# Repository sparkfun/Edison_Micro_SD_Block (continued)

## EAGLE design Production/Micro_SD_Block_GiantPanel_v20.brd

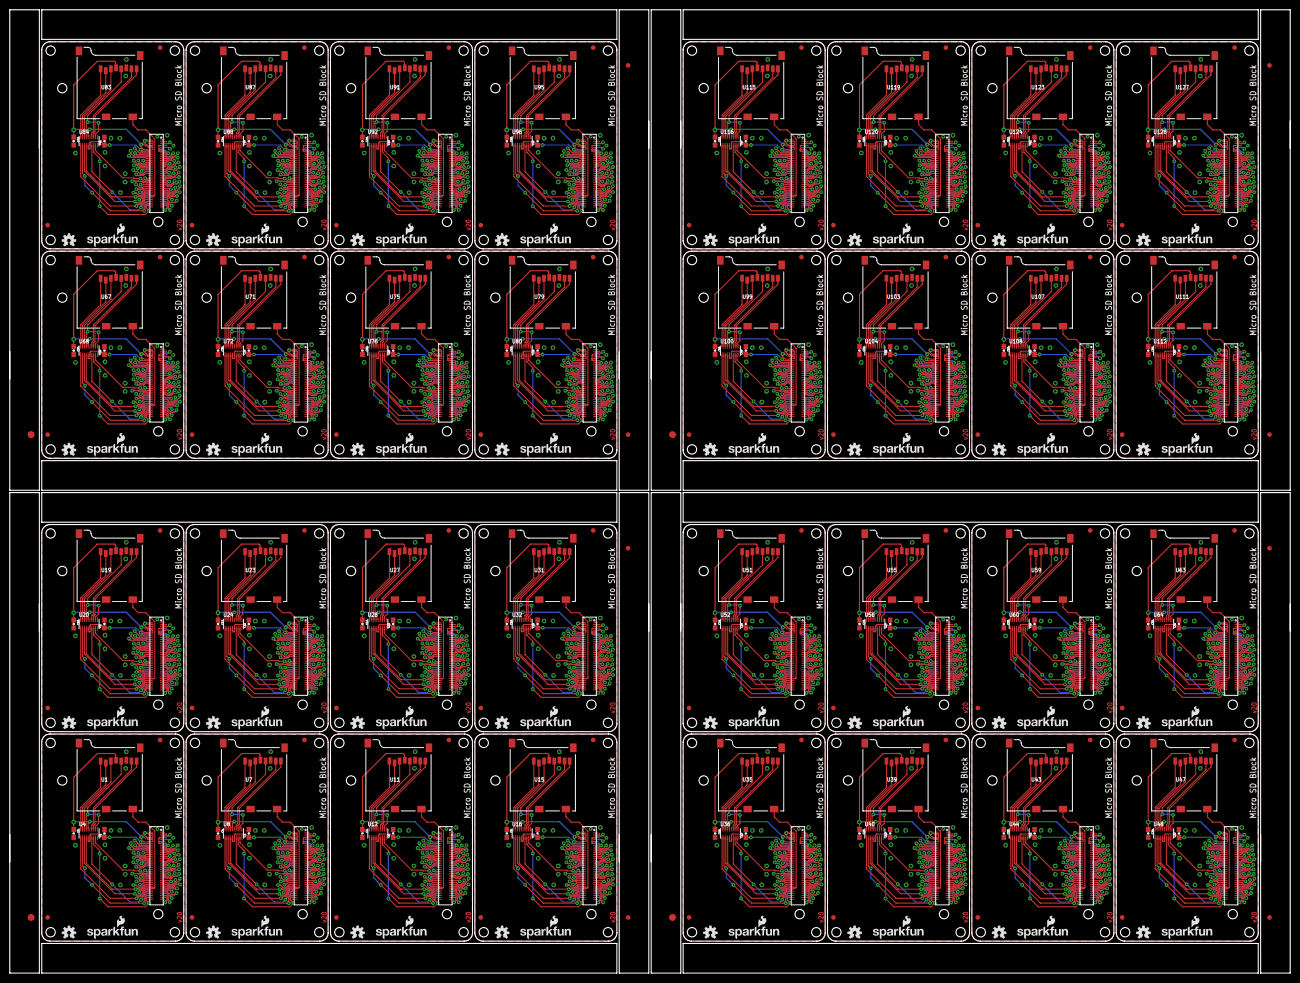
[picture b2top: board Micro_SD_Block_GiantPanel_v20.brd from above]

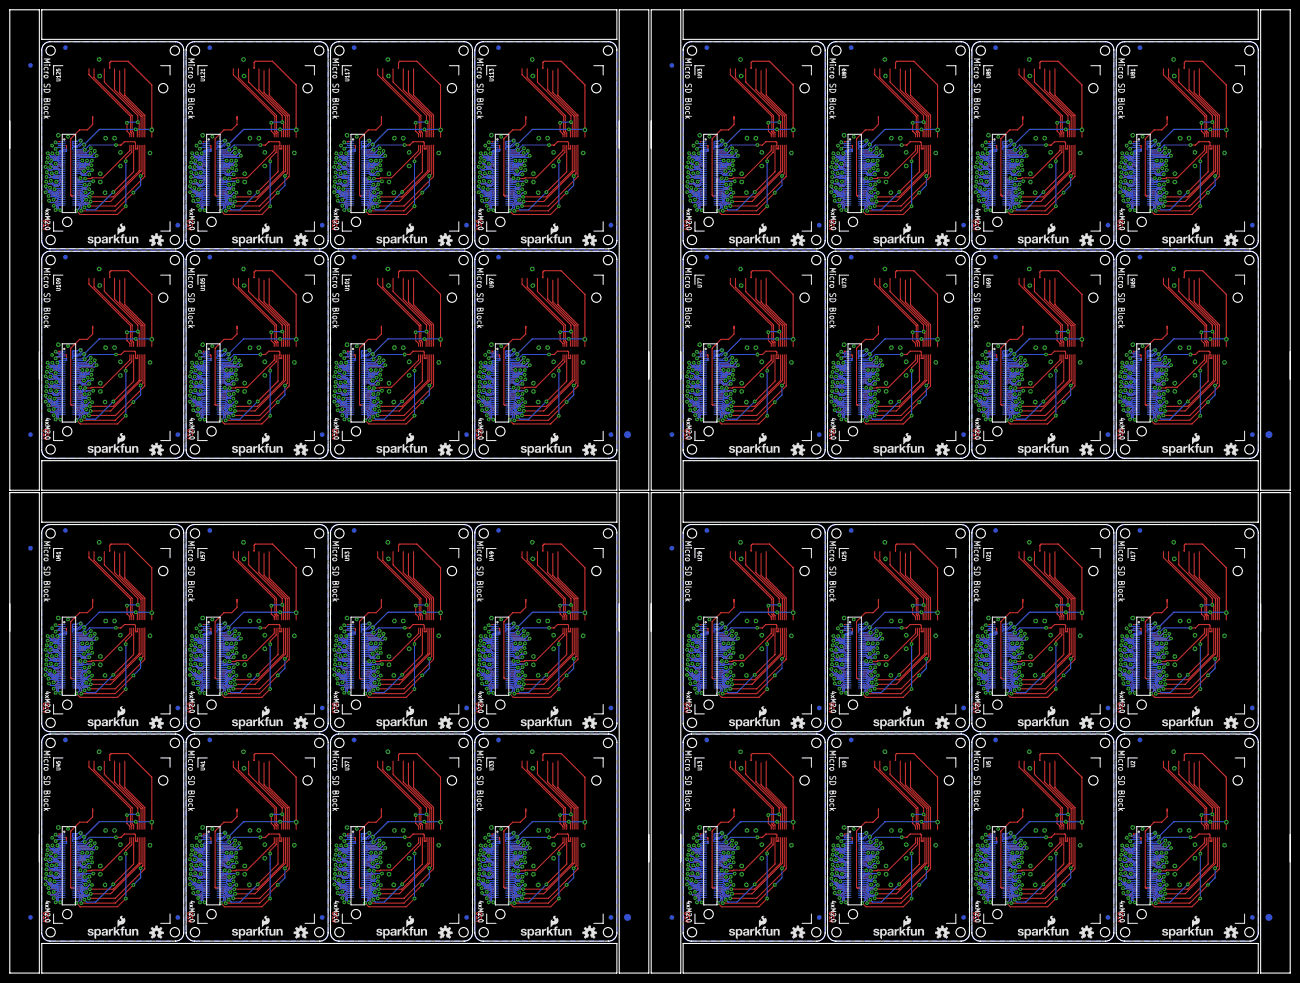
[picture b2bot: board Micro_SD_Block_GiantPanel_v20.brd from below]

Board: 2 copper layers, 274.8 x 206.8 mm, 472 parts (204 on the bottom side), 2048 nets.

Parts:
C1, C2, C3, C4, C5, C6, C7, C8, C9, C10, C11, C12, C13, C14, C15, C16, C17, C18, C19, C20, C21, C22, C23, C24, C25, C26, C27, C28, C29, C30, C31, C32, C33, C34, C35, C36, C37, C38, C39, C40, C41, C42, C43, C44, C45, C46, C47, C48, C49, C50, C51, C52, C53, C54, C55, C56, C57, C58, C59, C60, C61, C62, C63, C64: 0.1uF; 0603-CAP
E$1, E$2, E$9, E$10, E$15, E$16, E$21, E$22: FIDUCIAL-1.5X3
E$3, E$4, E$5, E$6, E$7, E$8, E$11, E$12, E$13, E$14, E$17, E$18, E$19, E$20, E$23, E$24: FIDUCIAL-1X2
FID1, FID2, FID3, FID4, FID5, FID6, FID7, FID8, FID9, FID10, FID11, FID12, FID13, FID14, FID15, FID16, FID17, FID18, FID19, FID20, FID21, FID22, FID23, FID24, FID25, FID26, FID27, FID28, FID29, FID30, FID31, FID32, FID33, FID34, FID35, FID36, FID37, FID38, FID39, FID40, FID41, FID42, FID43, FID44, FID45, FID46, FID47, FID48, FID49, FID50, FID51, FID52, FID53, FID54, FID55, FID56, FID57, FID58, FID59, FID60, FID61, FID62, FID63, FID64, FID65, FID66, FID67, FID68, FID69, FID70, FID71, FID72, FID73, FID74, FID75, FID76, FID77, FID78, FID79, FID80, FID81, FID82, FID83, FID84, FID85, FID86, FID87, FID88, FID89, FID90, FID91, FID92, FID93, FID94, FID95, FID96, FID97, FID98, FID99, FID100, FID101, FID102, FID103, FID104, FID105, FID106, FID107, FID108, FID109, FID110, FID111, FID112, FID113, FID114, FID115, FID116, FID117, FID118, FID119, FID120, FID121, FID122, FID123, FID124, FID125, FID126, FID127, FID128: FIDUCIAL1X2; FIDUCIAL-1X2
LOGO1, LOGO2, LOGO5, LOGO7, LOGO9, LOGO11, LOGO13, LOGO15, LOGO17, LOGO19, LOGO21, LOGO23, LOGO25, LOGO27, LOGO29, LOGO31, LOGO33, LOGO35, LOGO37, LOGO39, LOGO41, LOGO43, LOGO45, LOGO47, LOGO49, LOGO51, LOGO53, LOGO55, LOGO57, LOGO59, LOGO61, LOGO63, LOGO65, LOGO67, LOGO69, LOGO71, LOGO73, LOGO75, LOGO77, LOGO79, LOGO81, LOGO83, LOGO85, LOGO87, LOGO89, LOGO91, LOGO93, LOGO95, LOGO97, LOGO99, LOGO101, LOGO103, LOGO105, LOGO107, LOGO109, LOGO111, LOGO113, LOGO115, LOGO117, LOGO119, LOGO121, LOGO123, LOGO125, LOGO127: OSHW-LOGOS; OSHW-LOGO-S
LOGO3, LOGO4, LOGO6, LOGO8, LOGO10, LOGO12, LOGO14, LOGO16, LOGO18, LOGO20, LOGO22, LOGO24, LOGO26, LOGO28, LOGO30, LOGO32, LOGO34, LOGO36, LOGO38, LOGO40, LOGO42, LOGO44, LOGO46, LOGO48, LOGO50, LOGO52, LOGO54, LOGO56, LOGO58, LOGO60, LOGO62, LOGO64, LOGO66, LOGO68, LOGO70, LOGO72, LOGO74, LOGO76, LOGO78, LOGO80, LOGO82, LOGO84, LOGO86, LOGO88, LOGO90, LOGO92, LOGO94, LOGO96, LOGO98, LOGO100, LOGO102, LOGO104, LOGO106, LOGO108, LOGO110, LOGO112, LOGO114, LOGO116, LOGO118, LOGO120, LOGO122, LOGO124, LOGO126, LOGO128: SFE_LOGO_NAME_FLAME.1_INCH; SFE_LOGO_NAME_FLAME_.1
U1, U7, U11, U15, U19, U23, U27, U31, U35, U39, U43, U47, U51, U55, U59, U63, U67, U71, U75, U79, U83, U87, U91, U95, U99, U103, U107, U111, U115, U119, U123, U127: USD-SOCKETNEW; MICRO-SD-SOCKET-PP
U2, U5, U9, U13, U17, U21, U25, U29, U33, U37, U41, U45, U49, U53, U57, U61, U65, U69, U73, U77, U81, U85, U89, U93, U97, U101, U105, U109, U113, U117, U121, U125: EDISON_CONNECTOR_FULLMOUNTING_HOLES; EDISON_DAUGHTER
U3, U6, U10, U14, U18, U22, U26, U30, U34, U38, U42, U46, U50, U54, U58, U62, U66, U70, U74, U78, U82, U86, U90, U94, U98, U102, U106, U110, U114, U118, U122, U126: EDISON_CONNECTOR_FULLHEADER; DF40C-70DP-0.4(51)
U4, U8, U12, U16, U20, U24, U28, U32, U36, U40, U44, U48, U52, U56, U60, U64, U68, U72, U76, U80, U84, U88, U92, U96, U100, U104, U108, U112, U116, U120, U124, U128: TXB0108; UFDFN-20

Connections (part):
1.8V: C1.1, U2.12, U3.12, U4.P$5, U4.P$6
1.8V1: C3.1, U5.12, U6.12, U8.P$5, U8.P$6
1.8V2: C5.1, U9.12, U10.12, U12.P$5, U12.P$6
1.8V3: C7.1, U13.12, U14.12, U16.P$5, U16.P$6
1.8V4: C9.1, U17.12, U18.12, U20.P$5, U20.P$6
1.8V5: C11.1, U21.12, U22.12, U24.P$5, U24.P$6
1.8V6: C13.1, U25.12, U26.12, U28.P$5, U28.P$6
1.8V7: C15.1, U29.12, U30.12, U32.P$5, U32.P$6
1.8V8: C17.1, U33.12, U34.12, U36.P$5, U36.P$6
1.8V9: C19.1, U37.12, U38.12, U40.P$5, U40.P$6
1.8V10: C21.1, U41.12, U42.12, U44.P$5, U44.P$6
1.8V11: C23.1, U45.12, U46.12, U48.P$5, U48.P$6
1.8V12: C25.1, U49.12, U50.12, U52.P$5, U52.P$6
1.8V13: C27.1, U53.12, U54.12, U56.P$5, U56.P$6
1.8V14: C29.1, U57.12, U58.12, U60.P$5, U60.P$6
1.8V15: C31.1, U61.12, U62.12, U64.P$5, U64.P$6
1.8V16: C33.1, U65.12, U66.12, U68.P$5, U68.P$6
1.8V17: C35.1, U69.12, U70.12, U72.P$5, U72.P$6
1.8V18: C37.1, U73.12, U74.12, U76.P$5, U76.P$6
1.8V19: C39.1, U77.12, U78.12, U80.P$5, U80.P$6
1.8V20: C41.1, U81.12, U82.12, U84.P$5, U84.P$6
1.8V21: C43.1, U85.12, U86.12, U88.P$5, U88.P$6
1.8V22: C45.1, U89.12, U90.12, U92.P$5, U92.P$6
1.8V23: C47.1, U93.12, U94.12, U96.P$5, U96.P$6
1.8V24: C49.1, U97.12, U98.12, U100.P$5, U100.P$6
1.8V25: C51.1, U101.12, U102.12, U104.P$5, U104.P$6
1.8V26: C53.1, U105.12, U106.12, U108.P$5, U108.P$6
1.8V27: C55.1, U109.12, U110.12, U112.P$5, U112.P$6
1.8V28: C57.1, U113.12, U114.12, U116.P$5, U116.P$6
1.8V29: C59.1, U117.12, U118.12, U120.P$5, U120.P$6
1.8V30: C61.1, U121.12, U122.12, U124.P$5, U124.P$6
1.8V31: C63.1, U125.12, U126.12, U128.P$5, U128.P$6
3.3V: C2.1, U1.4, U2.8, U2.10, U3.8, U3.10, U4.P$16
3.3V1: C4.1, U5.8, U5.10, U6.8, U6.10, U7.4, U8.P$16
3.3V2: C6.1, U9.8, U9.10, U10.8, U10.10, U11.4, U12.P$16
3.3V3: C8.1, U13.8, U13.10, U14.8, U14.10, U15.4, U16.P$16
3.3V4: C10.1, U17.8, U17.10, U18.8, U18.10, U19.4, U20.P$16
3.3V5: C12.1, U21.8, U21.10, U22.8, U22.10, U23.4, U24.P$16
3.3V6: C14.1, U25.8, U25.10, U26.8, U26.10, U27.4, U28.P$16
3.3V7: C16.1, U29.8, U29.10, U30.8, U30.10, U31.4, U32.P$16
3.3V8: C18.1, U33.8, U33.10, U34.8, U34.10, U35.4, U36.P$16
3.3V9: C20.1, U37.8, U37.10, U38.8, U38.10, U39.4, U40.P$16
3.3V10: C22.1, U41.8, U41.10, U42.8, U42.10, U43.4, U44.P$16
3.3V11: C24.1, U45.8, U45.10, U46.8, U46.10, U47.4, U48.P$16
3.3V12: C26.1, U49.8, U49.10, U50.8, U50.10, U51.4, U52.P$16
3.3V13: C28.1, U53.8, U53.10, U54.8, U54.10, U55.4, U56.P$16
3.3V14: C30.1, U57.8, U57.10, U58.8, U58.10, U59.4, U60.P$16
3.3V15: C32.1, U61.8, U61.10, U62.8, U62.10, U63.4, U64.P$16
3.3V16: C34.1, U65.8, U65.10, U66.8, U66.10, U67.4, U68.P$16
3.3V17: C36.1, U69.8, U69.10, U70.8, U70.10, U71.4, U72.P$16
3.3V18: C38.1, U73.8, U73.10, U74.8, U74.10, U75.4, U76.P$16
3.3V19: C40.1, U77.8, U77.10, U78.8, U78.10, U79.4, U80.P$16
3.3V20: C42.1, U81.8, U81.10, U82.8, U82.10, U83.4, U84.P$16
3.3V21: C44.1, U85.8, U85.10, U86.8, U86.10, U87.4, U88.P$16
3.3V22: C46.1, U89.8, U89.10, U90.8, U90.10, U91.4, U92.P$16
3.3V23: C48.1, U93.8, U93.10, U94.8, U94.10, U95.4, U96.P$16
3.3V24: C50.1, U97.8, U97.10, U98.8, U98.10, U99.4, U100.P$16
3.3V25: C52.1, U101.8, U101.10, U102.8, U102.10, U103.4, U104.P$16
3.3V26: C54.1, U105.8, U105.10, U106.8, U106.10, U107.4, U108.P$16
3.3V27: C56.1, U109.8, U109.10, U110.8, U110.10, U111.4, U112.P$16
3.3V28: C58.1, U113.8, U113.10, U114.8, U114.10, U115.4, U116.P$16
3.3V29: C60.1, U117.8, U117.10, U118.8, U118.10, U119.4, U120.P$16
3.3V30: C62.1, U121.8, U121.10, U122.8, U122.10, U123.4, U124.P$16
3.3V31: C64.1, U125.8, U125.10, U126.8, U126.10, U127.4, U128.P$16
DCIN: U2.14, U3.14
DCIN1: U5.14, U6.14
DCIN2: U9.14, U10.14
DCIN3: U13.14, U14.14
DCIN4: U17.14, U18.14
DCIN5: U21.14, U22.14
DCIN6: U25.14, U26.14
DCIN7: U29.14, U30.14
DCIN8: U33.14, U34.14
DCIN9: U37.14, U38.14
DCIN10: U41.14, U42.14
DCIN11: U45.14, U46.14
DCIN12: U49.14, U50.14
DCIN13: U53.14, U54.14
DCIN14: U57.14, U58.14
DCIN15: U61.14, U62.14
DCIN16: U65.14, U66.14
DCIN17: U69.14, U70.14
DCIN18: U73.14, U74.14
DCIN19: U77.14, U78.14
DCIN20: U81.14, U82.14
DCIN21: U85.14, U86.14
DCIN22: U89.14, U90.14
DCIN23: U93.14, U94.14
DCIN24: U97.14, U98.14
DCIN25: U101.14, U102.14
DCIN26: U105.14, U106.14
DCIN27: U109.14, U110.14
DCIN28: U113.14, U114.14
DCIN29: U117.14, U118.14
DCIN30: U121.14, U122.14
DCIN31: U125.14, U126.14
FAULT: U2.19, U3.19
FAULT1: U5.19, U6.19
FAULT2: U9.19, U10.19
FAULT3: U13.19, U14.19
FAULT4: U17.19, U18.19
FAULT5: U21.19, U22.19
FAULT6: U25.19, U26.19
FAULT7: U29.19, U30.19
FAULT8: U33.19, U34.19
FAULT9: U37.19, U38.19
FAULT10: U41.19, U42.19
FAULT11: U45.19, U46.19
FAULT12: U49.19, U50.19
FAULT13: U53.19, U54.19
FAULT14: U57.19, U58.19
FAULT15: U61.19, U62.19
FAULT16: U65.19, U66.19
FAULT17: U69.19, U70.19
FAULT18: U73.19, U74.19
FAULT19: U77.19, U78.19
FAULT20: U81.19, U82.19
FAULT21: U85.19, U86.19
FAULT22: U89.19, U90.19
FAULT23: U93.19, U94.19
FAULT24: U97.19, U98.19
FAULT25: U101.19, U102.19
FAULT26: U105.19, U106.19
FAULT27: U109.19, U110.19
FAULT28: U113.19, U114.19
FAULT29: U117.19, U118.19
FAULT30: U121.19, U122.19
FAULT31: U125.19, U126.19
FW_RCVR: U2.69, U3.69
FW_RCVR1: U5.69, U6.69
FW_RCVR2: U9.69, U10.69
FW_RCVR3: U13.69, U14.69
FW_RCVR4: U17.69, U18.69
FW_RCVR5: U21.69, U22.69
FW_RCVR6: U25.69, U26.69
FW_RCVR7: U29.69, U30.69
FW_RCVR8: U33.69, U34.69
FW_RCVR9: U37.69, U38.69
FW_RCVR10: U41.69, U42.69
FW_RCVR11: U45.69, U46.69
FW_RCVR12: U49.69, U50.69
FW_RCVR13: U53.69, U54.69
FW_RCVR14: U57.69, U58.69
FW_RCVR15: U61.69, U62.69
FW_RCVR16: U65.69, U66.69
FW_RCVR17: U69.69, U70.69
FW_RCVR18: U73.69, U74.69
FW_RCVR19: U77.69, U78.69
FW_RCVR20: U81.69, U82.69
FW_RCVR21: U85.69, U86.69
FW_RCVR22: U89.69, U90.69
FW_RCVR23: U93.69, U94.69
FW_RCVR24: U97.69, U98.69
FW_RCVR25: U101.69, U102.69
FW_RCVR26: U105.69, U106.69
FW_RCVR27: U109.69, U110.69
FW_RCVR28: U113.69, U114.69
FW_RCVR29: U117.69, U118.69
FW_RCVR30: U121.69, U122.69
FW_RCVR31: U125.69, U126.69
GND: C1.2, C2.2, U1.6, U1.GND1, U1.GND3, U2.1, U2.5, U2.9, U2.11, U2.13, U2.15, U3.1, U3.5, U3.9, U3.11, U3.13, U3.15, U4.P$15
GND1: C3.2, C4.2, U5.1, U5.5, U5.9, U5.11, U5.13, U5.15, U6.1, U6.5, U6.9, U6.11, U6.13, U6.15, U7.6, U7.GND1, U7.GND3, U8.P$15
GND2: C5.2, C6.2, U9.1, U9.5, U9.9, U9.11, U9.13, U9.15, U10.1, U10.5, U10.9, U10.11, U10.13, U10.15, U11.6, U11.GND1, U11.GND3, U12.P$15
GND3: C7.2, C8.2, U13.1, U13.5, U13.9, U13.11, U13.13, U13.15, U14.1, U14.5, U14.9, U14.11, U14.13, U14.15, U15.6, U15.GND1, U15.GND3, U16.P$15
GND4: C9.2, C10.2, U17.1, U17.5, U17.9, U17.11, U17.13, U17.15, U18.1, U18.5, U18.9, U18.11, U18.13, U18.15, U19.6, U19.GND1, U19.GND3, U20.P$15
GND5: C11.2, C12.2, U21.1, U21.5, U21.9, U21.11, U21.13, U21.15, U22.1, U22.5, U22.9, U22.11, U22.13, U22.15, U23.6, U23.GND1, U23.GND3, U24.P$15
GND6: C13.2, C14.2, U25.1, U25.5, U25.9, U25.11, U25.13, U25.15, U26.1, U26.5, U26.9, U26.11, U26.13, U26.15, U27.6, U27.GND1, U27.GND3, U28.P$15
GND7: C15.2, C16.2, U29.1, U29.5, U29.9, U29.11, U29.13, U29.15, U30.1, U30.5, U30.9, U30.11, U30.13, U30.15, U31.6, U31.GND1, U31.GND3, U32.P$15
GND8: C17.2, C18.2, U33.1, U33.5, U33.9, U33.11, U33.13, U33.15, U34.1, U34.5, U34.9, U34.11, U34.13, U34.15, U35.6, U35.GND1, U35.GND3, U36.P$15
GND9: C19.2, C20.2, U37.1, U37.5, U37.9, U37.11, U37.13, U37.15, U38.1, U38.5, U38.9, U38.11, U38.13, U38.15, U39.6, U39.GND1, U39.GND3, U40.P$15
GND10: C21.2, C22.2, U41.1, U41.5, U41.9, U41.11, U41.13, U41.15, U42.1, U42.5, U42.9, U42.11, U42.13, U42.15, U43.6, U43.GND1, U43.GND3, U44.P$15
GND11: C23.2, C24.2, U45.1, U45.5, U45.9, U45.11, U45.13, U45.15, U46.1, U46.5, U46.9, U46.11, U46.13, U46.15, U47.6, U47.GND1, U47.GND3, U48.P$15
GND12: C25.2, C26.2, U49.1, U49.5, U49.9, U49.11, U49.13, U49.15, U50.1, U50.5, U50.9, U50.11, U50.13, U50.15, U51.6, U51.GND1, U51.GND3, U52.P$15
GND13: C27.2, C28.2, U53.1, U53.5, U53.9, U53.11, U53.13, U53.15, U54.1, U54.5, U54.9, U54.11, U54.13, U54.15, U55.6, U55.GND1, U55.GND3, U56.P$15
GND14: C29.2, C30.2, U57.1, U57.5, U57.9, U57.11, U57.13, U57.15, U58.1, U58.5, U58.9, U58.11, U58.13, U58.15, U59.6, U59.GND1, U59.GND3, U60.P$15
GND15: C31.2, C32.2, U61.1, U61.5, U61.9, U61.11, U61.13, U61.15, U62.1, U62.5, U62.9, U62.11, U62.13, U62.15, U63.6, U63.GND1, U63.GND3, U64.P$15
GND16: C33.2, C34.2, U65.1, U65.5, U65.9, U65.11, U65.13, U65.15, U66.1, U66.5, U66.9, U66.11, U66.13, U66.15, U67.6, U67.GND1, U67.GND3, U68.P$15
GND17: C35.2, C36.2, U69.1, U69.5, U69.9, U69.11, U69.13, U69.15, U70.1, U70.5, U70.9, U70.11, U70.13, U70.15, U71.6, U71.GND1, U71.GND3, U72.P$15
GND18: C37.2, C38.2, U73.1, U73.5, U73.9, U73.11, U73.13, U73.15, U74.1, U74.5, U74.9, U74.11, U74.13, U74.15, U75.6, U75.GND1, U75.GND3, U76.P$15
GND19: C39.2, C40.2, U77.1, U77.5, U77.9, U77.11, U77.13, U77.15, U78.1, U78.5, U78.9, U78.11, U78.13, U78.15, U79.6, U79.GND1, U79.GND3, U80.P$15
GND20: C41.2, C42.2, U81.1, U81.5, U81.9, U81.11, U81.13, U81.15, U82.1, U82.5, U82.9, U82.11, U82.13, U82.15, U83.6, U83.GND1, U83.GND3, U84.P$15
GND21: C43.2, C44.2, U85.1, U85.5, U85.9, U85.11, U85.13, U85.15, U86.1, U86.5, U86.9, U86.11, U86.13, U86.15, U87.6, U87.GND1, U87.GND3, U88.P$15
GND22: C45.2, C46.2, U89.1, U89.5, U89.9, U89.11, U89.13, U89.15, U90.1, U90.5, U90.9, U90.11, U90.13, U90.15, U91.6, U91.GND1, U91.GND3, U92.P$15
GND23: C47.2, C48.2, U93.1, U93.5, U93.9, U93.11, U93.13, U93.15, U94.1, U94.5, U94.9, U94.11, U94.13, U94.15, U95.6, U95.GND1, U95.GND3, U96.P$15
GND24: C49.2, C50.2, U97.1, U97.5, U97.9, U97.11, U97.13, U97.15, U98.1, U98.5, U98.9, U98.11, U98.13, U98.15, U99.6, U99.GND1, U99.GND3, U100.P$15
GND25: C51.2, C52.2, U101.1, U101.5, U101.9, U101.11, U101.13, U101.15, U102.1, U102.5, U102.9, U102.11, U102.13, U102.15, U103.6, U103.GND1, U103.GND3, U104.P$15
GND26: C53.2, C54.2, U105.1, U105.5, U105.9, U105.11, U105.13, U105.15, U106.1, U106.5, U106.9, U106.11, U106.13, U106.15, U107.6, U107.GND1, U107.GND3, U108.P$15
GND27: C55.2, C56.2, U109.1, U109.5, U109.9, U109.11, U109.13, U109.15, U110.1, U110.5, U110.9, U110.11, U110.13, U110.15, U111.6, U111.GND1, U111.GND3, U112.P$15
GND28: C57.2, C58.2, U113.1, U113.5, U113.9, U113.11, U113.13, U113.15, U114.1, U114.5, U114.9, U114.11, U114.13, U114.15, U115.6, U115.GND1, U115.GND3, U116.P$15
GND29: C59.2, C60.2, U117.1, U117.5, U117.9, U117.11, U117.13, U117.15, U118.1, U118.5, U118.9, U118.11, U118.13, U118.15, U119.6, U119.GND1, U119.GND3, U120.P$15
GND30: C61.2, C62.2, U121.1, U121.5, U121.9, U121.11, U121.13, U121.15, U122.1, U122.5, U122.9, U122.11, U122.13, U122.15, U123.6, U123.GND1, U123.GND3, U124.P$15
GND31: C63.2, C64.2, U125.1, U125.5, U125.9, U125.11, U125.13, U125.15, U126.1, U126.5, U126.9, U126.11, U126.13, U126.15, U127.6, U127.GND1, U127.GND3, U128.P$15
GP1: U5.48, U6.48
GP2: U5.42, U6.42
GP3: U5.34, U6.34
GP4: U5.32, U6.32
GP5: U5.30, U6.30
GP6: U5.28, U6.28
GP7: U5.26, U6.26
GP8: U5.25, U6.25
GP9: U5.24, U6.24
GP10: U9.48, U10.48
GP11: U9.42, U10.42
GP12: U9.34, U10.34
GP12_PWM0: U2.35, U3.35
GP12_PWM1: U5.35, U6.35
GP12_PWM2: U9.35, U10.35
GP12_PWM3: U13.35, U14.35
GP12_PWM4: U17.35, U18.35
GP12_PWM5: U21.35, U22.35
GP12_PWM6: U25.35, U26.35
GP12_PWM7: U29.35, U30.35
GP12_PWM8: U33.35, U34.35
GP12_PWM9: U37.35, U38.35
GP12_PWM10: U41.35, U42.35
GP12_PWM11: U45.35, U46.35
GP12_PWM12: U49.35, U50.35
GP12_PWM13: U53.35, U54.35
GP12_PWM14: U57.35, U58.35
GP12_PWM15: U61.35, U62.35
GP12_PWM16: U65.35, U66.35
GP12_PWM17: U69.35, U70.35
GP12_PWM18: U73.35, U74.35
GP12_PWM19: U77.35, U78.35
GP12_PWM20: U81.35, U82.35
GP12_PWM21: U85.35, U86.35
GP12_PWM22: U89.35, U90.35
GP12_PWM23: U93.35, U94.35
GP12_PWM24: U97.35, U98.35
GP12_PWM25: U101.35, U102.35
GP12_PWM26: U105.35, U106.35
GP12_PWM27: U109.35, U110.35
GP12_PWM28: U113.35, U114.35
GP12_PWM29: U117.35, U118.35
GP12_PWM30: U121.35, U122.35
GP12_PWM31: U125.35, U126.35
GP13: U9.32, U10.32
GP13_PWM1: U2.33, U3.33
GP13_PWM2: U5.33, U6.33
GP13_PWM3: U9.33, U10.33
GP13_PWM4: U13.33, U14.33
GP13_PWM5: U17.33, U18.33
GP13_PWM6: U21.33, U22.33
GP13_PWM7: U25.33, U26.33
GP13_PWM8: U29.33, U30.33
GP13_PWM9: U33.33, U34.33
GP13_PWM10: U37.33, U38.33
GP13_PWM11: U41.33, U42.33
GP13_PWM12: U45.33, U46.33
GP13_PWM13: U49.33, U50.33
GP13_PWM14: U53.33, U54.33
GP13_PWM15: U57.33, U58.33
GP13_PWM16: U61.33, U62.33
GP13_PWM17: U65.33, U66.33
GP13_PWM18: U69.33, U70.33
GP13_PWM19: U73.33, U74.33
GP13_PWM20: U77.33, U78.33
GP13_PWM21: U81.33, U82.33
GP13_PWM22: U85.33, U86.33
GP13_PWM23: U89.33, U90.33
GP13_PWM24: U93.33, U94.33
GP13_PWM25: U97.33, U98.33
GP13_PWM26: U101.33, U102.33
GP13_PWM27: U105.33, U106.33
GP13_PWM28: U109.33, U110.33
GP13_PWM29: U113.33, U114.33
GP13_PWM30: U117.33, U118.33
GP13_PWM31: U121.33, U122.33
GP13_PWM32: U125.33, U126.33
GP14: U2.48, U3.48
GP15: U2.42, U3.42
GP16: U9.30, U10.30
GP17: U9.28, U10.28
GP18: U9.26, U10.26
GP19: U9.25, U10.25
GP19_I2C_1_SCL: U2.41, U3.41
GP19_I2C_1_SCL1: U5.41, U6.41
GP19_I2C_1_SCL2: U9.41, U10.41
GP19_I2C_1_SCL3: U13.41, U14.41
GP19_I2C_1_SCL4: U17.41, U18.41
GP19_I2C_1_SCL5: U21.41, U22.41
GP19_I2C_1_SCL6: U25.41, U26.41
GP19_I2C_1_SCL7: U29.41, U30.41
GP19_I2C_1_SCL8: U33.41, U34.41
GP19_I2C_1_SCL9: U37.41, U38.41
GP19_I2C_1_SCL10: U41.41, U42.41
GP19_I2C_1_SCL11: U45.41, U46.41
GP19_I2C_1_SCL12: U49.41, U50.41
GP19_I2C_1_SCL13: U53.41, U54.41
GP19_I2C_1_SCL14: U57.41, U58.41
GP19_I2C_1_SCL15: U61.41, U62.41
GP19_I2C_1_SCL16: U65.41, U66.41
GP19_I2C_1_SCL17: U69.41, U70.41
GP19_I2C_1_SCL18: U73.41, U74.41
GP19_I2C_1_SCL19: U77.41, U78.41
GP19_I2C_1_SCL20: U81.41, U82.41
GP19_I2C_1_SCL21: U85.41, U86.41
GP19_I2C_1_SCL22: U89.41, U90.41
GP19_I2C_1_SCL23: U93.41, U94.41
GP19_I2C_1_SCL24: U97.41, U98.41
GP19_I2C_1_SCL25: U101.41, U102.41
GP19_I2C_1_SCL26: U105.41, U106.41
GP19_I2C_1_SCL27: U109.41, U110.41
GP19_I2C_1_SCL28: U113.41, U114.41
GP19_I2C_1_SCL29: U117.41, U118.41
GP19_I2C_1_SCL30: U121.41, U122.41
GP19_I2C_1_SCL31: U125.41, U126.41
GP20: U9.24, U10.24
GP20_I2C_1_SDA: U2.43, U3.43
GP20_I2C_1_SDA1: U5.43, U6.43
GP20_I2C_1_SDA2: U9.43, U10.43
GP20_I2C_1_SDA3: U13.43, U14.43
GP20_I2C_1_SDA4: U17.43, U18.43
GP20_I2C_1_SDA5: U21.43, U22.43
GP20_I2C_1_SDA6: U25.43, U26.43
GP20_I2C_1_SDA7: U29.43, U30.43
GP20_I2C_1_SDA8: U33.43, U34.43
GP20_I2C_1_SDA9: U37.43, U38.43
GP20_I2C_1_SDA10: U41.43, U42.43
GP20_I2C_1_SDA11: U45.43, U46.43
GP20_I2C_1_SDA12: U49.43, U50.43
GP20_I2C_1_SDA13: U53.43, U54.43
GP20_I2C_1_SDA14: U57.43, U58.43
GP20_I2C_1_SDA15: U61.43, U62.43
GP20_I2C_1_SDA16: U65.43, U66.43
GP20_I2C_1_SDA17: U69.43, U70.43
GP20_I2C_1_SDA18: U73.43, U74.43
GP20_I2C_1_SDA19: U77.43, U78.43
GP20_I2C_1_SDA20: U81.43, U82.43
GP20_I2C_1_SDA21: U85.43, U86.43
GP20_I2C_1_SDA22: U89.43, U90.43
GP20_I2C_1_SDA23: U93.43, U94.43
GP20_I2C_1_SDA24: U97.43, U98.43
GP20_I2C_1_SDA25: U101.43, U102.43
GP20_I2C_1_SDA26: U105.43, U106.43
GP20_I2C_1_SDA27: U109.43, U110.43
GP20_I2C_1_SDA28: U113.43, U114.43
GP20_I2C_1_SDA29: U117.43, U118.43
GP20_I2C_1_SDA30: U121.43, U122.43
GP20_I2C_1_SDA31: U125.43, U126.43
GP21: U13.48, U14.48
GP22: U13.42, U14.42
GP23: U13.34, U14.34
GP24: U13.32, U14.32
GP25: U13.30, U14.30
GP26: U13.28, U14.28
GP27: U13.26, U14.26
GP27_I2C_6_SCL: U2.45, U3.45
GP27_I2C_6_SCL1: U5.45, U6.45
GP27_I2C_6_SCL2: U9.45, U10.45
GP27_I2C_6_SCL3: U13.45, U14.45
GP27_I2C_6_SCL4: U17.45, U18.45
GP27_I2C_6_SCL5: U21.45, U22.45
GP27_I2C_6_SCL6: U25.45, U26.45
GP27_I2C_6_SCL7: U29.45, U30.45
GP27_I2C_6_SCL8: U33.45, U34.45
GP27_I2C_6_SCL9: U37.45, U38.45
GP27_I2C_6_SCL10: U41.45, U42.45
GP27_I2C_6_SCL11: U45.45, U46.45
GP27_I2C_6_SCL12: U49.45, U50.45
GP27_I2C_6_SCL13: U53.45, U54.45
GP27_I2C_6_SCL14: U57.45, U58.45
GP27_I2C_6_SCL15: U61.45, U62.45
GP27_I2C_6_SCL16: U65.45, U66.45
GP27_I2C_6_SCL17: U69.45, U70.45
GP27_I2C_6_SCL18: U73.45, U74.45
GP27_I2C_6_SCL19: U77.45, U78.45
GP27_I2C_6_SCL20: U81.45, U82.45
GP27_I2C_6_SCL21: U85.45, U86.45
GP27_I2C_6_SCL22: U89.45, U90.45
GP27_I2C_6_SCL23: U93.45, U94.45
GP27_I2C_6_SCL24: U97.45, U98.45
GP27_I2C_6_SCL25: U101.45, U102.45
GP27_I2C_6_SCL26: U105.45, U106.45
GP27_I2C_6_SCL27: U109.45, U110.45
GP27_I2C_6_SCL28: U113.45, U114.45
GP27_I2C_6_SCL29: U117.45, U118.45
GP27_I2C_6_SCL30: U121.45, U122.45
GP27_I2C_6_SCL31: U125.45, U126.45
GP28: U13.25, U14.25
GP28_I2C_6_SDA: U2.47, U3.47
GP28_I2C_6_SDA1: U5.47, U6.47
GP28_I2C_6_SDA2: U9.47, U10.47
GP28_I2C_6_SDA3: U13.47, U14.47
GP28_I2C_6_SDA4: U17.47, U18.47
GP28_I2C_6_SDA5: U21.47, U22.47
GP28_I2C_6_SDA6: U25.47, U26.47
GP28_I2C_6_SDA7: U29.47, U30.47
GP28_I2C_6_SDA8: U33.47, U34.47
GP28_I2C_6_SDA9: U37.47, U38.47
GP28_I2C_6_SDA10: U41.47, U42.47
GP28_I2C_6_SDA11: U45.47, U46.47
GP28_I2C_6_SDA12: U49.47, U50.47
GP28_I2C_6_SDA13: U53.47, U54.47
GP28_I2C_6_SDA14: U57.47, U58.47
GP28_I2C_6_SDA15: U61.47, U62.47
GP28_I2C_6_SDA16: U65.47, U66.47
GP28_I2C_6_SDA17: U69.47, U70.47
GP28_I2C_6_SDA18: U73.47, U74.47
GP28_I2C_6_SDA19: U77.47, U78.47
GP28_I2C_6_SDA20: U81.47, U82.47
GP28_I2C_6_SDA21: U85.47, U86.47
GP28_I2C_6_SDA22: U89.47, U90.47
GP28_I2C_6_SDA23: U93.47, U94.47
GP28_I2C_6_SDA24: U97.47, U98.47
GP28_I2C_6_SDA25: U101.47, U102.47
GP28_I2C_6_SDA26: U105.47, U106.47
GP28_I2C_6_SDA27: U109.47, U110.47
GP28_I2C_6_SDA28: U113.47, U114.47
GP28_I2C_6_SDA29: U117.47, U118.47
GP28_I2C_6_SDA30: U121.47, U122.47
GP28_I2C_6_SDA31: U125.47, U126.47
GP29: U13.24, U14.24
GP30: U17.48, U18.48
GP31: U17.42, U18.42
GP32: U17.34, U18.34
GP33: U17.32, U18.32
GP34: U17.30, U18.30
GP35: U17.28, U18.28
GP36: U17.26, U18.26
GP37: U17.25, U18.25
GP38: U17.24, U18.24
GP39: U21.48, U22.48
GP40: U21.42, U22.42
GP40_I2S_2_CLK: U2.52, U3.52
GP40_I2S_2_CLK1: U5.52, U6.52
GP40_I2S_2_CLK2: U9.52, U10.52
GP40_I2S_2_CLK3: U13.52, U14.52
GP40_I2S_2_CLK4: U17.52, U18.52
GP40_I2S_2_CLK5: U21.52, U22.52
GP40_I2S_2_CLK6: U25.52, U26.52
GP40_I2S_2_CLK7: U29.52, U30.52
GP40_I2S_2_CLK8: U33.52, U34.52
GP40_I2S_2_CLK9: U37.52, U38.52
GP40_I2S_2_CLK10: U41.52, U42.52
GP40_I2S_2_CLK11: U45.52, U46.52
GP40_I2S_2_CLK12: U49.52, U50.52
GP40_I2S_2_CLK13: U53.52, U54.52
GP40_I2S_2_CLK14: U57.52, U58.52
GP40_I2S_2_CLK15: U61.52, U62.52
GP40_I2S_2_CLK16: U65.52, U66.52
GP40_I2S_2_CLK17: U69.52, U70.52
GP40_I2S_2_CLK18: U73.52, U74.52
GP40_I2S_2_CLK19: U77.52, U78.52
GP40_I2S_2_CLK20: U81.52, U82.52
GP40_I2S_2_CLK21: U85.52, U86.52
GP40_I2S_2_CLK22: U89.52, U90.52
GP40_I2S_2_CLK23: U93.52, U94.52
GP40_I2S_2_CLK24: U97.52, U98.52
GP40_I2S_2_CLK25: U101.52, U102.52
GP40_I2S_2_CLK26: U105.52, U106.52
GP40_I2S_2_CLK27: U109.52, U110.52
GP40_I2S_2_CLK28: U113.52, U114.52
GP40_I2S_2_CLK29: U117.52, U118.52
GP40_I2S_2_CLK30: U121.52, U122.52
GP40_I2S_2_CLK31: U125.52, U126.52
GP41: U21.34, U22.34
GP41_I2S_2_FS: U2.54, U3.54
GP41_I2S_2_FS1: U5.54, U6.54
GP41_I2S_2_FS2: U9.54, U10.54
GP41_I2S_2_FS3: U13.54, U14.54
GP41_I2S_2_FS4: U17.54, U18.54
GP41_I2S_2_FS5: U21.54, U22.54
GP41_I2S_2_FS6: U25.54, U26.54
GP41_I2S_2_FS7: U29.54, U30.54
GP41_I2S_2_FS8: U33.54, U34.54
GP41_I2S_2_FS9: U37.54, U38.54
GP41_I2S_2_FS10: U41.54, U42.54
GP41_I2S_2_FS11: U45.54, U46.54
GP41_I2S_2_FS12: U49.54, U50.54
GP41_I2S_2_FS13: U53.54, U54.54
GP41_I2S_2_FS14: U57.54, U58.54
GP41_I2S_2_FS15: U61.54, U62.54
GP41_I2S_2_FS16: U65.54, U66.54
GP41_I2S_2_FS17: U69.54, U70.54
GP41_I2S_2_FS18: U73.54, U74.54
GP41_I2S_2_FS19: U77.54, U78.54
GP41_I2S_2_FS20: U81.54, U82.54
GP41_I2S_2_FS21: U85.54, U86.54
GP41_I2S_2_FS22: U89.54, U90.54
GP41_I2S_2_FS23: U93.54, U94.54
GP41_I2S_2_FS24: U97.54, U98.54
GP41_I2S_2_FS25: U101.54, U102.54
GP41_I2S_2_FS26: U105.54, U106.54
GP41_I2S_2_FS27: U109.54, U110.54
GP41_I2S_2_FS28: U113.54, U114.54
GP41_I2S_2_FS29: U117.54, U118.54
GP41_I2S_2_FS30: U121.54, U122.54
GP41_I2S_2_FS31: U125.54, U126.54
GP42: U21.32, U22.32
GP42_I2S_2_RXD: U2.50, U3.50
GP42_I2S_2_RXD1: U5.50, U6.50
GP42_I2S_2_RXD2: U9.50, U10.50
GP42_I2S_2_RXD3: U13.50, U14.50
GP42_I2S_2_RXD4: U17.50, U18.50
GP42_I2S_2_RXD5: U21.50, U22.50
GP42_I2S_2_RXD6: U25.50, U26.50
GP42_I2S_2_RXD7: U29.50, U30.50
GP42_I2S_2_RXD8: U33.50, U34.50
GP42_I2S_2_RXD9: U37.50, U38.50
GP42_I2S_2_RXD10: U41.50, U42.50
GP42_I2S_2_RXD11: U45.50, U46.50
GP42_I2S_2_RXD12: U49.50, U50.50
GP42_I2S_2_RXD13: U53.50, U54.50
GP42_I2S_2_RXD14: U57.50, U58.50
GP42_I2S_2_RXD15: U61.50, U62.50
GP42_I2S_2_RXD16: U65.50, U66.50
GP42_I2S_2_RXD17: U69.50, U70.50
GP42_I2S_2_RXD18: U73.50, U74.50
GP42_I2S_2_RXD19: U77.50, U78.50
GP42_I2S_2_RXD20: U81.50, U82.50
GP42_I2S_2_RXD21: U85.50, U86.50
GP42_I2S_2_RXD22: U89.50, U90.50
GP42_I2S_2_RXD23: U93.50, U94.50
GP42_I2S_2_RXD24: U97.50, U98.50
GP42_I2S_2_RXD25: U101.50, U102.50
GP42_I2S_2_RXD26: U105.50, U106.50
GP42_I2S_2_RXD27: U109.50, U110.50
GP42_I2S_2_RXD28: U113.50, U114.50
GP42_I2S_2_RXD29: U117.50, U118.50
GP42_I2S_2_RXD30: U121.50, U122.50
GP42_I2S_2_RXD31: U125.50, U126.50
GP43: U21.30, U22.30
GP43_I2S_2_TXD: U2.56, U3.56
GP43_I2S_2_TXD1: U5.56, U6.56
GP43_I2S_2_TXD2: U9.56, U10.56
GP43_I2S_2_TXD3: U13.56, U14.56
GP43_I2S_2_TXD4: U17.56, U18.56
GP43_I2S_2_TXD5: U21.56, U22.56
GP43_I2S_2_TXD6: U25.56, U26.56
GP43_I2S_2_TXD7: U29.56, U30.56
GP43_I2S_2_TXD8: U33.56, U34.56
GP43_I2S_2_TXD9: U37.56, U38.56
GP43_I2S_2_TXD10: U41.56, U42.56
GP43_I2S_2_TXD11: U45.56, U46.56
GP43_I2S_2_TXD12: U49.56, U50.56
GP43_I2S_2_TXD13: U53.56, U54.56
GP43_I2S_2_TXD14: U57.56, U58.56
GP43_I2S_2_TXD15: U61.56, U62.56
GP43_I2S_2_TXD16: U65.56, U66.56
GP43_I2S_2_TXD17: U69.56, U70.56
GP43_I2S_2_TXD18: U73.56, U74.56
GP43_I2S_2_TXD19: U77.56, U78.56
GP43_I2S_2_TXD20: U81.56, U82.56
GP43_I2S_2_TXD21: U85.56, U86.56
GP43_I2S_2_TXD22: U89.56, U90.56
GP43_I2S_2_TXD23: U93.56, U94.56
GP43_I2S_2_TXD24: U97.56, U98.56
GP43_I2S_2_TXD25: U101.56, U102.56
GP43_I2S_2_TXD26: U105.56, U106.56
GP43_I2S_2_TXD27: U109.56, U110.56
GP43_I2S_2_TXD28: U113.56, U114.56
GP43_I2S_2_TXD29: U117.56, U118.56
GP43_I2S_2_TXD30: U121.56, U122.56
GP43_I2S_2_TXD31: U125.56, U126.56
GP44: U2.24, U3.24
GP45: U2.26, U3.26
GP46: U2.28, U3.28
GP47: U2.30, U3.30
GP48: U2.32, U3.32
GP49: U2.34, U3.34
GP50: U21.28, U22.28
GP51: U21.26, U22.26
GP52: U21.25, U22.25
GP53: U21.24, U22.24
GP54: U25.48, U26.48
GP55: U25.42, U26.42
GP56: U25.34, U26.34
GP57: U25.32, U26.32
GP58: U25.30, U26.30
GP59: U25.28, U26.28
GP60: U25.26, U26.26
GP61: U25.25, U26.25
GP62: U25.24, U26.24
GP63: U29.48, U30.48
GP64: U29.42, U30.42
GP65: U29.34, U30.34
GP66: U29.32, U30.32
GP67: U29.30, U30.30
GP68: U29.28, U30.28
GP69: U29.26, U30.26
GP70: U29.25, U30.25
GP71: U29.24, U30.24
GP72: U33.48, U34.48
GP73: U33.42, U34.42
GP74: U33.34, U34.34
GP75: U33.32, U34.32
GP76: U33.30, U34.30
GP77: U33.28, U34.28
GP77_SD_0_CD#: U1.CD1, U2.60, U3.60
GP77_SD_0_CD#1: U5.60, U6.60, U7.CD1
GP77_SD_0_CD#2: U9.60, U10.60, U11.CD1
GP77_SD_0_CD#3: U13.60, U14.60, U15.CD1
GP77_SD_0_CD#4: U17.60, U18.60, U19.CD1
GP77_SD_0_CD#5: U21.60, U22.60, U23.CD1
GP77_SD_0_CD#6: U25.60, U26.60, U27.CD1
GP77_SD_0_CD#7: U29.60, U30.60, U31.CD1
GP77_SD_0_CD#8: U33.60, U34.60, U35.CD1
GP77_SD_0_CD#9: U37.60, U38.60, U39.CD1
GP77_SD_0_CD#10: U41.60, U42.60, U43.CD1
GP77_SD_0_CD#11: U45.60, U46.60, U47.CD1
GP77_SD_0_CD#12: U49.60, U50.60, U51.CD1
GP77_SD_0_CD#13: U53.60, U54.60, U55.CD1
GP77_SD_0_CD#14: U57.60, U58.60, U59.CD1
GP77_SD_0_CD#15: U61.60, U62.60, U63.CD1
GP77_SD_0_CD#16: U65.60, U66.60, U67.CD1
GP77_SD_0_CD#17: U69.60, U70.60, U71.CD1
GP77_SD_0_CD#18: U73.60, U74.60, U75.CD1
GP77_SD_0_CD#19: U77.60, U78.60, U79.CD1
GP77_SD_0_CD#20: U81.60, U82.60, U83.CD1
GP77_SD_0_CD#21: U85.60, U86.60, U87.CD1
GP77_SD_0_CD#22: U89.60, U90.60, U91.CD1
GP77_SD_0_CD#23: U93.60, U94.60, U95.CD1
GP77_SD_0_CD#24: U97.60, U98.60, U99.CD1
GP77_SD_0_CD#25: U101.60, U102.60, U103.CD1
GP77_SD_0_CD#26: U105.60, U106.60, U107.CD1
GP77_SD_0_CD#27: U109.60, U110.60, U111.CD1
GP77_SD_0_CD#28: U113.60, U114.60, U115.CD1
GP77_SD_0_CD#29: U117.60, U118.60, U119.CD1
GP77_SD_0_CD#30: U121.60, U122.60, U123.CD1
GP77_SD_0_CD#31: U125.60, U126.60, U127.CD1
GP78: U33.26, U34.26
GP78_SD_0_CLK: U2.58, U3.58, U4.P$4
GP78_SD_0_CLK1: U5.58, U6.58, U8.P$4
GP78_SD_0_CLK2: U9.58, U10.58, U12.P$4
GP78_SD_0_CLK3: U13.58, U14.58, U16.P$4
GP78_SD_0_CLK4: U17.58, U18.58, U20.P$4
GP78_SD_0_CLK5: U21.58, U22.58, U24.P$4
GP78_SD_0_CLK6: U25.58, U26.58, U28.P$4
GP78_SD_0_CLK7: U29.58, U30.58, U32.P$4
GP78_SD_0_CLK8: U33.58, U34.58, U36.P$4
GP78_SD_0_CLK9: U37.58, U38.58, U40.P$4
GP78_SD_0_CLK10: U41.58, U42.58, U44.P$4
GP78_SD_0_CLK11: U45.58, U46.58, U48.P$4
GP78_SD_0_CLK12: U49.58, U50.58, U52.P$4
GP78_SD_0_CLK13: U53.58, U54.58, U56.P$4
GP78_SD_0_CLK14: U57.58, U58.58, U60.P$4
GP78_SD_0_CLK15: U61.58, U62.58, U64.P$4
GP78_SD_0_CLK16: U65.58, U66.58, U68.P$4
GP78_SD_0_CLK17: U69.58, U70.58, U72.P$4
GP78_SD_0_CLK18: U73.58, U74.58, U76.P$4
GP78_SD_0_CLK19: U77.58, U78.58, U80.P$4
GP78_SD_0_CLK20: U81.58, U82.58, U84.P$4
GP78_SD_0_CLK21: U85.58, U86.58, U88.P$4
GP78_SD_0_CLK22: U89.58, U90.58, U92.P$4
GP78_SD_0_CLK23: U93.58, U94.58, U96.P$4
GP78_SD_0_CLK24: U97.58, U98.58, U100.P$4
GP78_SD_0_CLK25: U101.58, U102.58, U104.P$4
GP78_SD_0_CLK26: U105.58, U106.58, U108.P$4
GP78_SD_0_CLK27: U109.58, U110.58, U112.P$4
GP78_SD_0_CLK28: U113.58, U114.58, U116.P$4
GP78_SD_0_CLK29: U117.58, U118.58, U120.P$4
GP78_SD_0_CLK30: U121.58, U122.58, U124.P$4
GP78_SD_0_CLK31: U125.58, U126.58, U128.P$4
GP79: U33.25, U34.25
GP79_SD_0_CMD: U2.62, U3.62, U4.P$3
GP79_SD_0_CMD1: U5.62, U6.62, U8.P$3
GP79_SD_0_CMD2: U9.62, U10.62, U12.P$3
GP79_SD_0_CMD3: U13.62, U14.62, U16.P$3
GP79_SD_0_CMD4: U17.62, U18.62, U20.P$3
GP79_SD_0_CMD5: U21.62, U22.62, U24.P$3
GP79_SD_0_CMD6: U25.62, U26.62, U28.P$3
GP79_SD_0_CMD7: U29.62, U30.62, U32.P$3
GP79_SD_0_CMD8: U33.62, U34.62, U36.P$3
GP79_SD_0_CMD9: U37.62, U38.62, U40.P$3
GP79_SD_0_CMD10: U41.62, U42.62, U44.P$3
GP79_SD_0_CMD11: U45.62, U46.62, U48.P$3
GP79_SD_0_CMD12: U49.62, U50.62, U52.P$3
GP79_SD_0_CMD13: U53.62, U54.62, U56.P$3
GP79_SD_0_CMD14: U57.62, U58.62, U60.P$3
GP79_SD_0_CMD15: U61.62, U62.62, U64.P$3
GP79_SD_0_CMD16: U65.62, U66.62, U68.P$3
GP79_SD_0_CMD17: U69.62, U70.62, U72.P$3
GP79_SD_0_CMD18: U73.62, U74.62, U76.P$3
GP79_SD_0_CMD19: U77.62, U78.62, U80.P$3
GP79_SD_0_CMD20: U81.62, U82.62, U84.P$3
GP79_SD_0_CMD21: U85.62, U86.62, U88.P$3
GP79_SD_0_CMD22: U89.62, U90.62, U92.P$3
GP79_SD_0_CMD23: U93.62, U94.62, U96.P$3
GP79_SD_0_CMD24: U97.62, U98.62, U100.P$3
GP79_SD_0_CMD25: U101.62, U102.62, U104.P$3
GP79_SD_0_CMD26: U105.62, U106.62, U108.P$3
GP79_SD_0_CMD27: U109.62, U110.62, U112.P$3
GP79_SD_0_CMD28: U113.62, U114.62, U116.P$3
GP79_SD_0_CMD29: U117.62, U118.62, U120.P$3
GP79_SD_0_CMD30: U121.62, U122.62, U124.P$3
GP79_SD_0_CMD31: U125.62, U126.62, U128.P$3
GP80: U33.24, U34.24
GP80_SD_0_DAT0: U2.66, U3.66, U4.P$7
GP80_SD_0_DAT1: U5.66, U6.66, U8.P$7
GP80_SD_0_DAT2: U9.66, U10.66, U12.P$7
GP80_SD_0_DAT3: U13.66, U14.66, U16.P$7
GP80_SD_0_DAT4: U17.66, U18.66, U20.P$7
GP80_SD_0_DAT5: U21.66, U22.66, U24.P$7
GP80_SD_0_DAT6: U25.66, U26.66, U28.P$7
GP80_SD_0_DAT7: U29.66, U30.66, U32.P$7
GP80_SD_0_DAT8: U33.66, U34.66, U36.P$7
GP80_SD_0_DAT9: U37.66, U38.66, U40.P$7
GP80_SD_0_DAT10: U41.66, U42.66, U44.P$7
GP80_SD_0_DAT11: U45.66, U46.66, U48.P$7
GP80_SD_0_DAT12: U49.66, U50.66, U52.P$7
GP80_SD_0_DAT13: U53.66, U54.66, U56.P$7
GP80_SD_0_DAT14: U57.66, U58.66, U60.P$7
GP80_SD_0_DAT15: U61.66, U62.66, U64.P$7
GP80_SD_0_DAT16: U65.66, U66.66, U68.P$7
GP80_SD_0_DAT17: U69.66, U70.66, U72.P$7
GP80_SD_0_DAT18: U73.66, U74.66, U76.P$7
GP80_SD_0_DAT19: U77.66, U78.66, U80.P$7
GP80_SD_0_DAT20: U81.66, U82.66, U84.P$7
GP80_SD_0_DAT21: U85.66, U86.66, U88.P$7
GP80_SD_0_DAT22: U89.66, U90.66, U92.P$7
GP80_SD_0_DAT23: U93.66, U94.66, U96.P$7
GP80_SD_0_DAT24: U97.66, U98.66, U100.P$7
GP80_SD_0_DAT25: U101.66, U102.66, U104.P$7
GP80_SD_0_DAT26: U105.66, U106.66, U108.P$7
GP80_SD_0_DAT27: U109.66, U110.66, U112.P$7
GP80_SD_0_DAT28: U113.66, U114.66, U116.P$7
GP80_SD_0_DAT29: U117.66, U118.66, U120.P$7
GP80_SD_0_DAT30: U121.66, U122.66, U124.P$7
GP80_SD_0_DAT31: U125.66, U126.66, U128.P$7
GP81: U37.48, U38.48
GP81_SD_0_DAT1: U2.70, U3.70, U4.P$8
GP81_SD_0_DAT2: U5.70, U6.70, U8.P$8
GP81_SD_0_DAT3: U9.70, U10.70, U12.P$8
GP81_SD_0_DAT4: U13.70, U14.70, U16.P$8
GP81_SD_0_DAT5: U17.70, U18.70, U20.P$8
GP81_SD_0_DAT6: U21.70, U22.70, U24.P$8
GP81_SD_0_DAT7: U25.70, U26.70, U28.P$8
GP81_SD_0_DAT8: U29.70, U30.70, U32.P$8
GP81_SD_0_DAT9: U33.70, U34.70, U36.P$8
GP81_SD_0_DAT10: U37.70, U38.70, U40.P$8
GP81_SD_0_DAT11: U41.70, U42.70, U44.P$8
GP81_SD_0_DAT12: U45.70, U46.70, U48.P$8
GP81_SD_0_DAT13: U49.70, U50.70, U52.P$8
GP81_SD_0_DAT14: U53.70, U54.70, U56.P$8
GP81_SD_0_DAT15: U57.70, U58.70, U60.P$8
GP81_SD_0_DAT16: U61.70, U62.70, U64.P$8
GP81_SD_0_DAT17: U65.70, U66.70, U68.P$8
GP81_SD_0_DAT18: U69.70, U70.70, U72.P$8
GP81_SD_0_DAT19: U73.70, U74.70, U76.P$8
GP81_SD_0_DAT20: U77.70, U78.70, U80.P$8
GP81_SD_0_DAT21: U81.70, U82.70, U84.P$8
GP81_SD_0_DAT22: U85.70, U86.70, U88.P$8
GP81_SD_0_DAT23: U89.70, U90.70, U92.P$8
GP81_SD_0_DAT24: U93.70, U94.70, U96.P$8
GP81_SD_0_DAT25: U97.70, U98.70, U100.P$8
GP81_SD_0_DAT26: U101.70, U102.70, U104.P$8
GP81_SD_0_DAT27: U105.70, U106.70, U108.P$8
GP81_SD_0_DAT28: U109.70, U110.70, U112.P$8
GP81_SD_0_DAT29: U113.70, U114.70, U116.P$8
GP81_SD_0_DAT30: U117.70, U118.70, U120.P$8
GP81_SD_0_DAT31: U121.70, U122.70, U124.P$8
GP81_SD_0_DAT32: U125.70, U126.70, U128.P$8
GP82: U37.42, U38.42
GP82_SD_0_DAT1: U5.64, U6.64, U8.P$1
GP82_SD_0_DAT2: U2.64, U3.64, U4.P$1
GP82_SD_0_DAT3: U9.64, U10.64, U12.P$1
GP82_SD_0_DAT4: U13.64, U14.64, U16.P$1
GP82_SD_0_DAT5: U17.64, U18.64, U20.P$1
GP82_SD_0_DAT6: U21.64, U22.64, U24.P$1
GP82_SD_0_DAT7: U25.64, U26.64, U28.P$1
GP82_SD_0_DAT8: U29.64, U30.64, U32.P$1
GP82_SD_0_DAT9: U33.64, U34.64, U36.P$1
GP82_SD_0_DAT10: U37.64, U38.64, U40.P$1
GP82_SD_0_DAT11: U41.64, U42.64, U44.P$1
GP82_SD_0_DAT12: U45.64, U46.64, U48.P$1
GP82_SD_0_DAT13: U49.64, U50.64, U52.P$1
GP82_SD_0_DAT14: U53.64, U54.64, U56.P$1
GP82_SD_0_DAT15: U57.64, U58.64, U60.P$1
GP82_SD_0_DAT16: U61.64, U62.64, U64.P$1
GP82_SD_0_DAT17: U65.64, U66.64, U68.P$1
GP82_SD_0_DAT18: U69.64, U70.64, U72.P$1
GP82_SD_0_DAT19: U73.64, U74.64, U76.P$1
GP82_SD_0_DAT20: U77.64, U78.64, U80.P$1
GP82_SD_0_DAT21: U81.64, U82.64, U84.P$1
GP82_SD_0_DAT22: U85.64, U86.64, U88.P$1
GP82_SD_0_DAT23: U89.64, U90.64, U92.P$1
GP82_SD_0_DAT24: U93.64, U94.64, U96.P$1
GP82_SD_0_DAT25: U97.64, U98.64, U100.P$1
GP82_SD_0_DAT26: U101.64, U102.64, U104.P$1
GP82_SD_0_DAT27: U105.64, U106.64, U108.P$1
GP82_SD_0_DAT28: U109.64, U110.64, U112.P$1
GP82_SD_0_DAT29: U113.64, U114.64, U116.P$1
GP82_SD_0_DAT30: U117.64, U118.64, U120.P$1
GP82_SD_0_DAT31: U121.64, U122.64, U124.P$1
GP82_SD_0_DAT32: U125.64, U126.64, U128.P$1
GP83: U37.34, U38.34
GP83_SD_0_DAT1: U5.68, U6.68, U8.P$2
GP83_SD_0_DAT2: U9.68, U10.68, U12.P$2
GP83_SD_0_DAT3: U2.68, U3.68, U4.P$2
GP83_SD_0_DAT4: U13.68, U14.68, U16.P$2
GP83_SD_0_DAT5: U17.68, U18.68, U20.P$2
GP83_SD_0_DAT6: U21.68, U22.68, U24.P$2
GP83_SD_0_DAT7: U25.68, U26.68, U28.P$2
GP83_SD_0_DAT8: U29.68, U30.68, U32.P$2
GP83_SD_0_DAT9: U33.68, U34.68, U36.P$2
GP83_SD_0_DAT10: U37.68, U38.68, U40.P$2
GP83_SD_0_DAT11: U41.68, U42.68, U44.P$2
GP83_SD_0_DAT12: U45.68, U46.68, U48.P$2
GP83_SD_0_DAT13: U49.68, U50.68, U52.P$2
GP83_SD_0_DAT14: U53.68, U54.68, U56.P$2
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
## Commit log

2014-08-09 initial commit with templates
2014-08-09 renamed template and added SD, still needs work for level shifting
2014-08-09 added fiducials
2014-08-11 Layout complete, Ready for review.
2014-08-11 added version numbers
2014-08-12 removed Edzzanine from name
2014-08-14 fixed OE to high
2014-09-23 work in progress
2014-09-25 Added DCIN pin cleaned up dimensions cleaned up names on board created clock feedback test circuit
2014-09-25 renamed files
2014-09-25 file cleanup
2014-10-16 removed thermals on connectors updated connector to new foot print updated version number corrected silk positions
2014-10-17 modified traces to eliminate bridging. Selected FB circuit to use in production.
2014-10-17 Moved 3.3v bus out from under highspeed lines updated edison connector footprint to remove jumpers removed jumpers from txb0108
    TODO: Remove P$#'s from txb0108 in library
2014-10-17 Ready for reds Struck one weird leftover via Renamed TXB0108 chip refdes To-do: fix the TXB0108 symbol to remove P$ from pin names. Do in library and update to design!
2014-10-22 created v10 panels
2014-12-17 fixed CD grounding issue, CD1 and CD2 are connected internally.
2014-12-18 removed v10 panels and created v20 panels
2015-04-01 Updating README, directory name
